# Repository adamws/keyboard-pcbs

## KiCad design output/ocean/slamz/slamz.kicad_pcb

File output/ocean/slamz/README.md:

## ocean/slamz

[layout](slamz-kle.json) - [PCB](slamz.kicad_pcb)

{:loading="lazy"}

[Open in keyboard-layout-editor](http://www.keyboard-layout-editor.com/##@@=0,0&=0,1&=0,2&=0,3&=0,4&_x:2;&=0,5&=0,6&=0,7&=0,8&=0,9;&@=1,0&=1,1&=1,2&=1,3&=1,4&_x:2;&=1,5&=1,6&=1,7&=1,8&=1,9;&@=2,0&=2,1&=2,2&=2,3&=2,4&_x:2;&=2,5&=2,6&=2,7&=2,8&=2,9;&@=3,0&=3,1&=3,2&=3,3%0A%0A%0A0,0&=3,4%0A%0A%0A0,0&_x:2;&=3,5%0A%0A%0A1,0&=3,6%0A%0A%0A1,0&=3,7&=3,8&=3,9;&@_x:3&y:0.25&w:2;&=3,4%0A%0A%0A0,1&_x:2&w:2;&=3,5%0A%0A%0A1,1)

{:loading="lazy"}

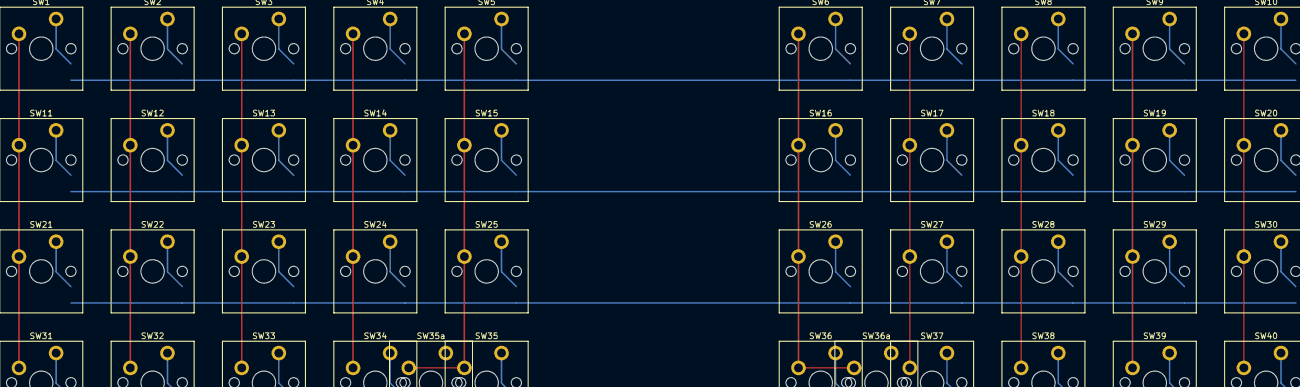
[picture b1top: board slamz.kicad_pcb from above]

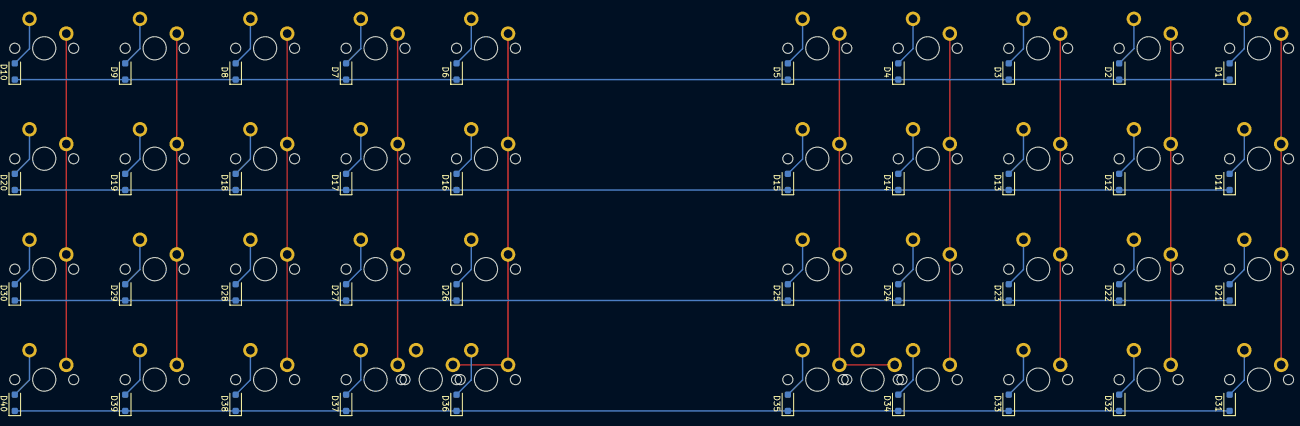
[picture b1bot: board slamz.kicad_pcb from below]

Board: 2 copper layers, 82 parts (40 on the bottom side), 54 nets.

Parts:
D1, D2, D3, D4, D5, D6, D7, D8, D9, D10, D11, D12, D13, D14, D15, D16, D17, D18, D19, D20, D21, D22, D23, D24, D25, D26, D27, D28, D29, D30, D31, D32, D33, D34, D35, D36, D37, D38, D39, D40: D_SOD-123F
SW1, SW2, SW3, SW4, SW5, SW6, SW7, SW8, SW9, SW10, SW11, SW12, SW13, SW14, SW15, SW16, SW17, SW18, SW19, SW20, SW21, SW22, SW23, SW24, SW25, SW26, SW27, SW28, SW29, SW30, SW31, SW32, SW33, SW34, SW35, SW35a, SW36, SW36a, SW37, SW38, SW39, SW40: SW_Cherry_MX_PCB_1.00u

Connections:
COL0: SW1.1, SW11.1, SW21.1, SW31.1
COL1: SW2.1, SW12.1, SW22.1, SW32.1
COL2: SW3.1, SW13.1, SW23.1, SW33.1
COL3: SW4.1, SW14.1, SW24.1, SW34.1
COL4: SW5.1, SW15.1, SW25.1, SW35.1, SW35a.1
COL5: SW6.1, SW16.1, SW26.1, SW36.1, SW36a.1
COL6: SW7.1, SW17.1, SW27.1, SW37.1
COL7: SW8.1, SW18.1, SW28.1, SW38.1
COL8: SW9.1, SW19.1, SW29.1, SW39.1
COL9: SW10.1, SW20.1, SW30.1, SW40.1
unnamed: D1.2, SW1.2
unnamed: D2.2, SW2.2
unnamed: D3.2, SW3.2
unnamed: D4.2, SW4.2
unnamed: D5.2, SW5.2
unnamed: D6.2, SW6.2
unnamed: D7.2, SW7.2
unnamed: D8.2, SW8.2
unnamed: D9.2, SW9.2
unnamed: D10.2, SW10.2
unnamed: D11.2, SW11.2
unnamed: D12.2, SW12.2
unnamed: D13.2, SW13.2
unnamed: D14.2, SW14.2
unnamed: D15.2, SW15.2
unnamed: D16.2, SW16.2
unnamed: D17.2, SW17.2
unnamed: D18.2, SW18.2
unnamed: D19.2, SW19.2
unnamed: D20.2, SW20.2
unnamed: D21.2, SW21.2
unnamed: D22.2, SW22.2
unnamed: D23.2, SW23.2
unnamed: D24.2, SW24.2
unnamed: D25.2, SW25.2
unnamed: D26.2, SW26.2
unnamed: D27.2, SW27.2
unnamed: D28.2, SW28.2
unnamed: D29.2, SW29.2
unnamed: D30.2, SW30.2
unnamed: D31.2, SW31.2
unnamed: D32.2, SW32.2
unnamed: D33.2, SW33.2
unnamed: D34.2, SW34.2
unnamed: D35.2, SW35.2, SW35a.2
unnamed: D36.2, SW36.2, SW36a.2
unnamed: D37.2, SW37.2
unnamed: D38.2, SW38.2
unnamed: D39.2, SW39.2
unnamed: D40.2, SW40.2
ROW0: D1.1, D2.1, D3.1, D4.1, D5.1, D6.1, D7.1, D8.1, D9.1, D10.1
ROW1: D11.1, D12.1, D13.1, D14.1, D15.1, D16.1, D17.1, D18.1, D19.1, D20.1
ROW2: D21.1, D22.1, D23.1, D24.1, D25.1, D26.1, D27.1, D28.1, D29.1, D30.1
ROW3: D31.1, D32.1, D33.1, D34.1, D35.1, D36.1, D37.1, D38.1, D39.1, D40.1

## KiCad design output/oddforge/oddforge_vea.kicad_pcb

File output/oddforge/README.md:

## oddforge/oddforge_vea

[layout](oddforge_vea-kle.json) - [PCB](oddforge_vea.kicad_pcb)

{:loading="lazy"}

[Open in keyboard-layout-editor](http://www.keyboard-layout-editor.com/##@@_x:2.25&c=#777777;&=5,0&_c=#aaaaaa;&=5,1&=5,2&=5,3&=5,4&=5,5&=5,6&_x:1.5;&=5,8&=5,9&=5,10&=5,11&=5,12&=5,13&=6,11&=7,11&=6,13;&@=6,1&=7,1&_x:0.25;&=4,0&_c=#cccccc;&=4,1&=4,2&=4,3&=4,4&=4,5&=4,6&_x:1.5;&=4,8&=4,9&=4,10&=4,11&=4,12&=4,13&_c=#aaaaaa&w:2;&=4,14&=6,10;&@=6,2&=7,2&_x:0.25&w:1.5;&=3,0&_c=#cccccc;&=3,1&=3,2&=3,3&=3,4&=3,5&_x:1.5;&=1,8&=1,9&=1,10&=1,11&=1,12&=1,13&=1,14&_c=#aaaaaa&w:1.5;&=2,14&=7,10;&@=6,3&=7,3&_x:0.25&w:1.75;&=2,0&_c=#cccccc;&=2,1&=2,2&=2,3&=2,4&=2,5&_x:1.5;&=2,8&=2,9&=2,10&=2,11&=2,12&=2,13&_c=#777777&w:2.25;&=3,13&_c=#aaaaaa;&=6,12;&@=6,4&=7,4&_x:0.25&w:2.25;&=1,0&_c=#cccccc;&=1,1&=1,2&=1,3&=1,4&=1,5&_x:1.5;&=3,8&=3,9&=3,10&=3,11&=3,12&_c=#aaaaaa&w:1.75;&=3,14&=6,8&=7,12;&@=6,5&=7,5&_x:0.25&w:1.25;&=0,0&_w:1.25;&=0,1&_w:1.25;&=0,2&=7,7&_w:2;&=6,6&_x:1.5&w:2.75;&=6,14&_w:1.25;&=0,10&=0,9&_w:1.25;&=0,8&=7,8&=6,9&=7,9)

{:loading="lazy"}

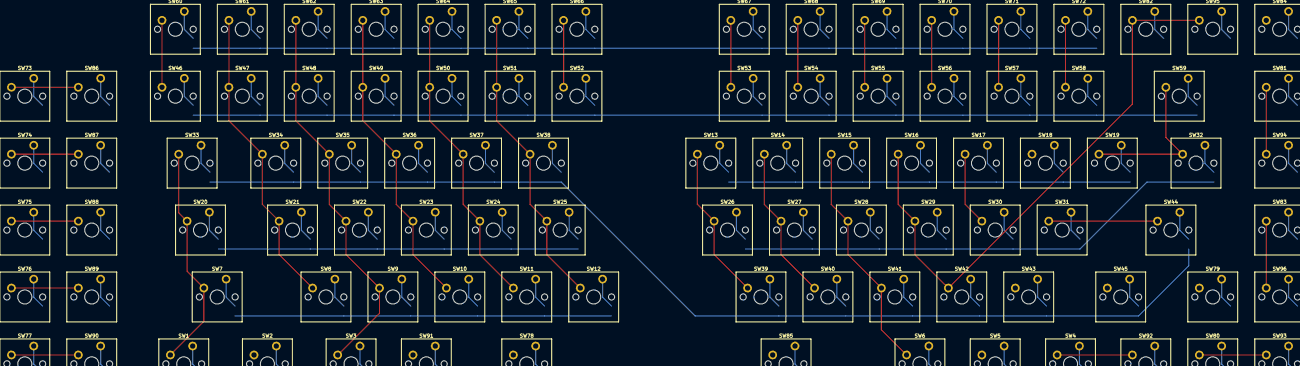
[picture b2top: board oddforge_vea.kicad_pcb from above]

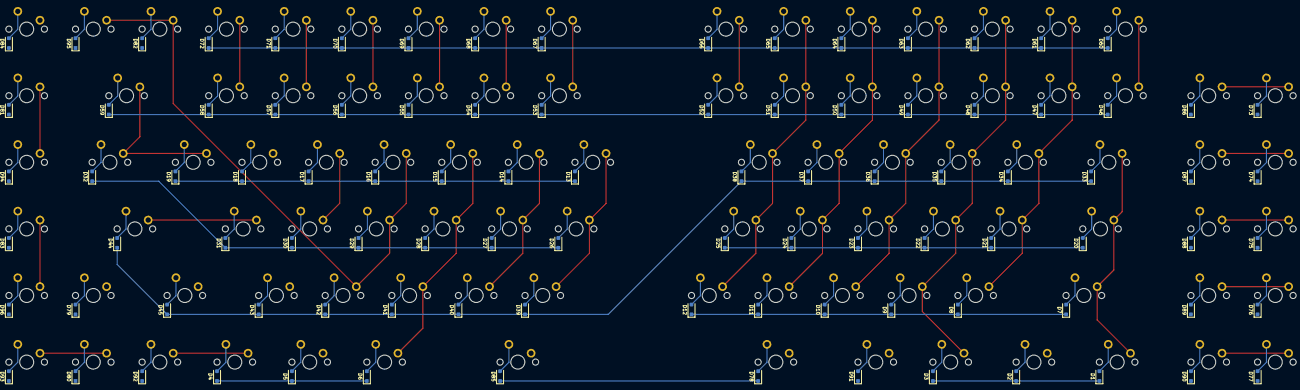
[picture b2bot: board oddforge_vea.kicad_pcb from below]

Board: 2 copper layers, 192 parts (96 on the bottom side), 118 nets.

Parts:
D1, D2, D3, D4, D5, D6, D7, D8, D9, D10, D11, D12, D13, D14, D15, D16, D17, D18, D19, D20, D21, D22, D23, D24, D25, D26, D27, D28, D29, D30, D31, D32, D33, D34, D35, D36, D37, D38, D39, D40, D41, D42, D43, D44, D45, D46, D47, D48, D49, D50, D51, D52, D53, D54, D55, D56, D57, D58, D59, D60, D61, D62, D63, D64, D65, D66, D67, D68, D69, D70, D71, D72, D73, D74, D75, D76, D77, D78, D79, D80, D81, D82, D83, D84, D85, D86, D87, D88, D89, D90, D91, D92, D93, D94, D95, D96: D_SOD-123F
SW1, SW2, SW3, SW4, SW5, SW6, SW7, SW8, SW9, SW10, SW11, SW12, SW13, SW14, SW15, SW16, SW17, SW18, SW19, SW20, SW21, SW22, SW23, SW24, SW25, SW26, SW27, SW28, SW29, SW30, SW31, SW32, SW33, SW34, SW35, SW36, SW37, SW38, SW39, SW40, SW41, SW42, SW43, SW44, SW45, SW46, SW47, SW48, SW49, SW50, SW51, SW52, SW53, SW54, SW55, SW56, SW57, SW58, SW59, SW60, SW61, SW62, SW63, SW64, SW65, SW66, SW67, SW68, SW69, SW70, SW71, SW72, SW73, SW74, SW75, SW76, SW77, SW78, SW79, SW80, SW81, SW82, SW83, SW84, SW85, SW86, SW87, SW88, SW89, SW90, SW91, SW92, SW93, SW94, SW95, SW96: SW_Cherry_MX_PCB_1.00u

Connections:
COL0: SW1.1, SW7.1, SW20.1, SW33.1, SW46.1, SW60.1
COL1: SW2.1, SW8.1, SW21.1, SW34.1, SW47.1, SW61.1, SW73.1, SW86.1
COL2: SW3.1, SW9.1, SW22.1, SW35.1, SW48.1, SW62.1, SW74.1, SW87.1
COL3: SW10.1, SW23.1, SW36.1, SW49.1, SW63.1, SW75.1, SW88.1
COL4: SW11.1, SW24.1, SW37.1, SW50.1, SW64.1, SW76.1, SW89.1
COL5: SW12.1, SW25.1, SW38.1, SW51.1, SW65.1, SW77.1, SW90.1
COL6: SW52.1, SW66.1, SW78.1
COL8: SW4.1, SW13.1, SW26.1, SW39.1, SW53.1, SW67.1, SW79.1, SW92.1
COL9: SW5.1, SW14.1, SW27.1, SW40.1, SW54.1, SW68.1, SW80.1, SW93.1
COL10: SW6.1, SW15.1, SW28.1, SW41.1, SW55.1, SW69.1, SW81.1, SW94.1
COL11: SW16.1, SW29.1, SW42.1, SW56.1, SW70.1, SW82.1, SW95.1
COL12: SW17.1, SW30.1, SW43.1, SW57.1, SW71.1, SW83.1, SW96.1
COL13: SW18.1, SW31.1, SW44.1, SW58.1, SW72.1, SW84.1
COL14: SW19.1, SW32.1, SW45.1, SW59.1, SW85.1
unnamed: D1.2, SW1.2
unnamed: D2.2, SW2.2
unnamed: D3.2, SW3.2
unnamed: D4.2, SW4.2
unnamed: D5.2, SW5.2
unnamed: D6.2, SW6.2
unnamed: D7.2, SW7.2
unnamed: D8.2, SW8.2
unnamed: D9.2, SW9.2
unnamed: D10.2, SW10.2
unnamed: D11.2, SW11.2
unnamed: D12.2, SW12.2
unnamed: D13.2, SW13.2
unnamed: D14.2, SW14.2
unnamed: D15.2, SW15.2
unnamed: D16.2, SW16.2
unnamed: D17.2, SW17.2
unnamed: D18.2, SW18.2
unnamed: D19.2, SW19.2
unnamed: D20.2, SW20.2
unnamed: D21.2, SW21.2
unnamed: D22.2, SW22.2
unnamed: D23.2, SW23.2
unnamed: D24.2, SW24.2
unnamed: D25.2, SW25.2
unnamed: D26.2, SW26.2
unnamed: D27.2, SW27.2
unnamed: D28.2, SW28.2
unnamed: D29.2, SW29.2
unnamed: D30.2, SW30.2
unnamed: D31.2, SW31.2
unnamed: D32.2, SW32.2
unnamed: D33.2, SW33.2
unnamed: D34.2, SW34.2
unnamed: D35.2, SW35.2
unnamed: D36.2, SW36.2
unnamed: D37.2, SW37.2
unnamed: D38.2, SW38.2
unnamed: D39.2, SW39.2
unnamed: D40.2, SW40.2
unnamed: D41.2, SW41.2
unnamed: D42.2, SW42.2
unnamed: D43.2, SW43.2
unnamed: D44.2, SW44.2
unnamed: D45.2, SW45.2
unnamed: D46.2, SW46.2
unnamed: D47.2, SW47.2
unnamed: D48.2, SW48.2
unnamed: D49.2, SW49.2
unnamed: D50.2, SW50.2
unnamed: D51.2, SW51.2
unnamed: D52.2, SW52.2
unnamed: D53.2, SW53.2
unnamed: D54.2, SW54.2
unnamed: D55.2, SW55.2
unnamed: D56.2, SW56.2
unnamed: D57.2, SW57.2
unnamed: D58.2, SW58.2
unnamed: D59.2, SW59.2
unnamed: D60.2, SW60.2
unnamed: D61.2, SW61.2
unnamed: D62.2, SW62.2
unnamed: D63.2, SW63.2
unnamed: D64.2, SW64.2
unnamed: D65.2, SW65.2
unnamed: D66.2, SW66.2
unnamed: D67.2, SW67.2
unnamed: D68.2, SW68.2
unnamed: D69.2, SW69.2
unnamed: D70.2, SW70.2
unnamed: D71.2, SW71.2
unnamed: D72.2, SW72.2
unnamed: D73.2, SW73.2
unnamed: D74.2, SW74.2
unnamed: D75.2, SW75.2
unnamed: D76.2, SW76.2
unnamed: D77.2, SW77.2
unnamed: D78.2, SW78.2
unnamed: D79.2, SW79.2
unnamed: D80.2, SW80.2
unnamed: D81.2, SW81.2
unnamed: D82.2, SW82.2
unnamed: D83.2, SW83.2
unnamed: D84.2, SW84.2
unnamed: D85.2, SW85.2
unnamed: D86.2, SW86.2
unnamed: D87.2, SW87.2
unnamed: D88.2, SW88.2
unnamed: D89.2, SW89.2
unnamed: D90.2, SW90.2
unnamed: D91.2, SW91.2
unnamed: D92.2, SW92.2
unnamed: D93.2, SW93.2
unnamed: D94.2, SW94.2
unnamed: D95.2, SW95.2
unnamed: D96.2, SW96.2
ROW0: D1.1, D2.1, D3.1, D4.1, D5.1, D6.1
ROW1: D7.1, D8.1, D9.1, D10.1, D11.1, D12.1, D13.1, D14.1, D15.1, D16.1, D17.1, D18.1, D19.1
ROW2: D20.1, D21.1, D22.1, D23.1, D24.1, D25.1, D26.1, D27.1, D28.1, D29.1, D30.1, D31.1, D32.1
ROW3: D33.1, D34.1, D35.1, D36.1, D37.1, D38.1, D39.1, D40.1, D41.1, D42.1, D43.1, D44.1, D45.1
ROW4: D46.1, D47.1, D48.1, D49.1, D50.1, D51.1, D52.1, D53.1, D54.1, D55.1, D56.1, D57.1, D58.1, D59.1
ROW5: D60.1, D61.1, D62.1, D63.1, D64.1, D65.1, D66.1, D67.1, D68.1, D69.1, D70.1, D71.1, D72.1
ROW6: D73.1, D74.1, D75.1, D76.1, D77.1, D78.1, D79.1, D80.1, D81.1, D82.1, D83.1, D84.1, D85.1
ROW7: D86.1, D87.1, D88.1, D89.1, D90.1, D91.1, D92.1, D93.1, D94.1, D95.1, D96.1
